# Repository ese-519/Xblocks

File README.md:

AtomWire
============

**University of Pennsylvania, ESE 519: Real Time and Embedded Systems**

* Siri Anil, Sana Kamboj, Sarvesh Patkar
* [Blog](https://devpost.com/software/atomwire) 

### [Demo](https://youtu.be/rHM-RSoe9MM)

### Chess

### Tower of Hanoi

### Instructions
Please follow the instructions in the report to run the system

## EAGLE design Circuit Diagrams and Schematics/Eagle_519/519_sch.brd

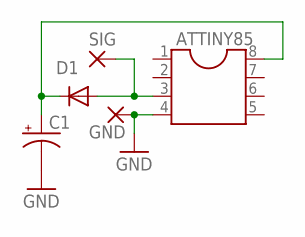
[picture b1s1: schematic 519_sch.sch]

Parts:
ATTINY85: DIL8; DIL08
C1: CPOL-USE2,5-6E; E2,5-6E
D1: 1N4148DO35-7; DO35-7
GND: 3,81/1,4
SIG: 3,81/1,4

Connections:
GND: ATTINY85.4, C1.-, GND.1
unnamed: ATTINY85.8, C1.+, D1.C
unnamed: ATTINY85.3, D1.A, SIG.1

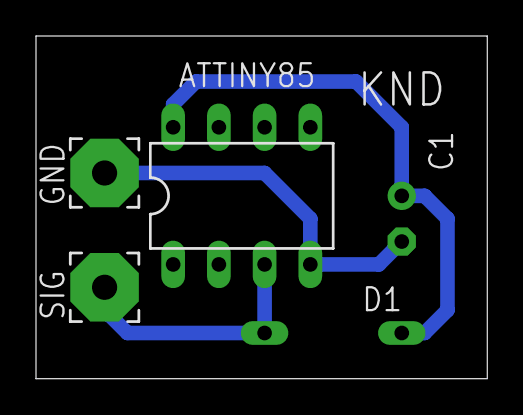
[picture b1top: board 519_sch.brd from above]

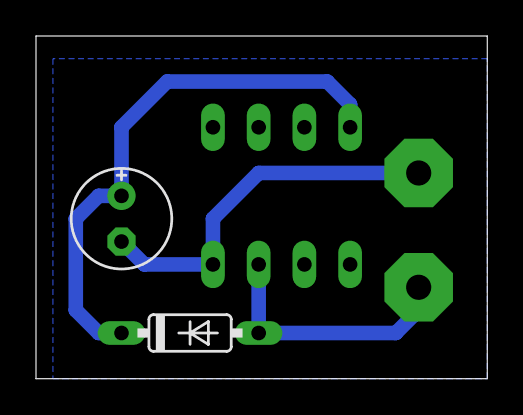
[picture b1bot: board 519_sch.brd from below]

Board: 2 copper layers, 25.1 x 19.0 mm, 5 parts (2 on the bottom side), 3 nets.

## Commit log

2016-11-22 Initial commit test
2016-11-22 Committed the game
